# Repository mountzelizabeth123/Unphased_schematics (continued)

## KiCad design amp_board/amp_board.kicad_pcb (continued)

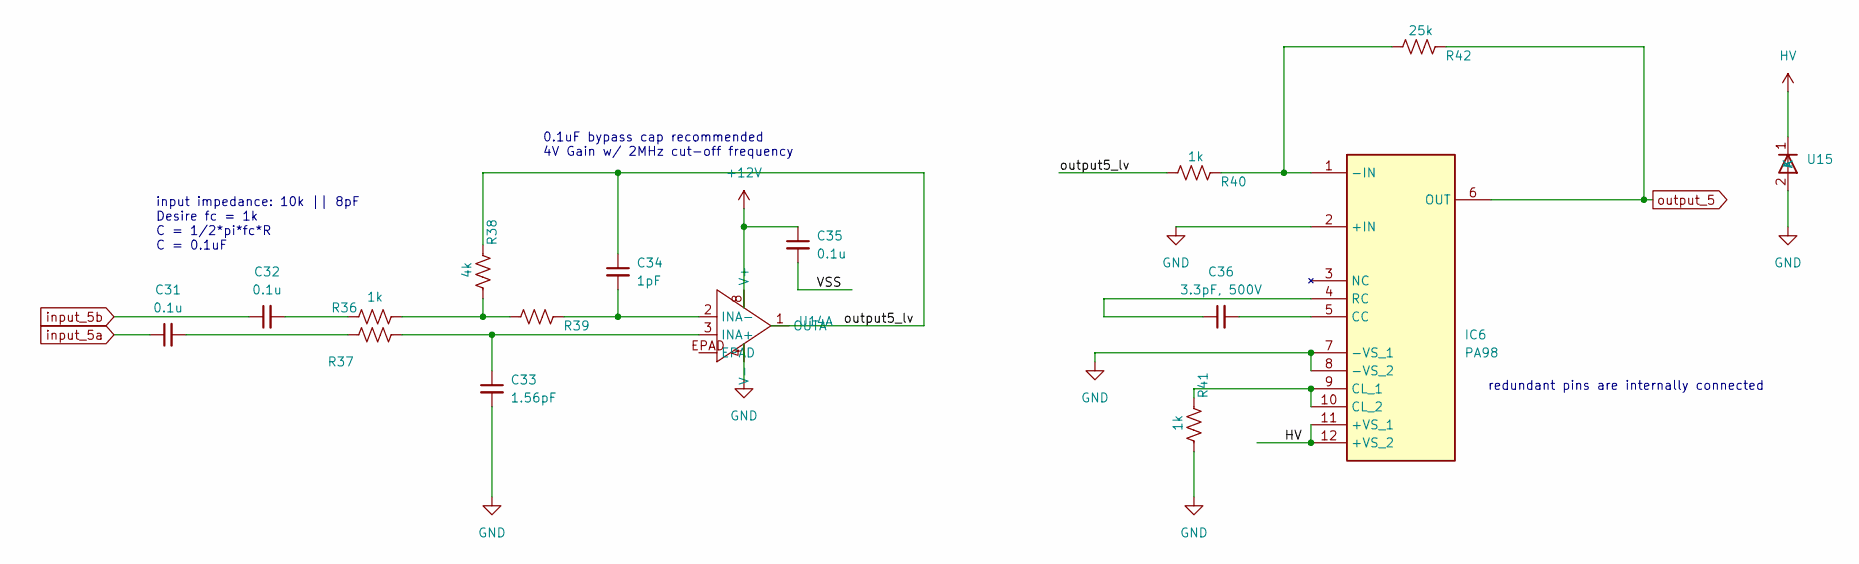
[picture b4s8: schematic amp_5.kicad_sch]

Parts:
C31, C32, C35: 0.1u; C_0603_1608Metric
C33: 1.56pF; C_0603_1608Metric
C34: 1pF; C_0603_1608Metric
C36: 3.3pF, 500V; C_0805_2012Metric
IC6: PA98; Mouser Part Number 137-PA98
R36, R40, R41: 1k; R_0603_1608Metric
R37, R39: R_US; R_0603_1608Metric
R38: 4k; R_0603_1608Metric
R42: 25k; R_0603_1608Metric
U14: OPA2211AIDDAR_L
U15: SMCJ150A-13-F

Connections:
+12V: C35.1, U14.8 (V+); also elsewhere on the board
/amp_5/VSS: C35.2
/amp_5/output5_lv: C34.1, R38.1, R40.2, U14.1 (OUTA)
GND: C33.2, IC6.2 (+IN), IC6.7 (-VS_1), IC6.8 (-VS_2), R41.2, U14.4 (V-), U15.2 (A); also elsewhere on the board
HV: IC6.11 (+VS_1), IC6.12 (+VS_2), U15.1 (K); also elsewhere on the board
unnamed: C31.2, R37.2
unnamed: C32.2, R36.2
unnamed: IC6.1 (-IN), R40.1, R42.2
unnamed: C36.2, IC6.5 (CC)
unnamed: IC6.9 (CL_1), IC6.10 (CL_2), R41.1
unnamed: C36.1, IC6.4 (RC)
unnamed: R36.1, R38.2, R39.2
unnamed: C33.1, R37.1, U14.3 (INA+)
unnamed: C34.2, R39.1, U14.2 (INA-)
input_5a: C31.1; also elsewhere on the board
input_5b: C32.1; also elsewhere on the board
output_5: IC6.6 (OUT), R42.1; also elsewhere on the board

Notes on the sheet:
redundant pins are internally connected
input impedance: 10k || 8pF Desire fc = 1k C = 1/2*pi*fc*R C = 0.1uF
0.1uF bypass cap recommended
4V Gain w/ 2MHz cut-off frequency

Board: 4 copper layers, 122 parts (0 on the bottom side), 81 nets, no tracks yet.

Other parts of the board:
J4, J6: SMA_RF2-04A-T-00-50-G; CONN_RF2-04A-T-00-50-G_ADM

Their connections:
GND: J4.2, J4.3 (Ext), J4.4 (Ext), J4.5 (Ext), J6.2, J6.3 (Ext), J6.4 (Ext), J6.5 (Ext); also elsewhere on the board
input_0a: J4.1; also elsewhere on the board
input_0b: J6.1; also elsewhere on the board

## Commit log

2024-09-24 Icurrent and ADC schem
2024-09-24 ADC swap for multi-channel opamp
2024-09-28 add .gitignore for kicad projects
2024-09-28 reorg repo
2024-09-28 added huxley; removed .DS_Store mac filesystem files from repo; add .DS_Store to .gitignore
2024-09-28 added blank README
2024-09-28 made the README a md file like it should have been
2024-09-28 added analog chip schematics and connector footprints
2024-09-29 updated Ibias gen and footprints
2024-09-29 updated footprints
2024-10-01 layout
2024-10-01 layout_1
2024-10-01 layout_2
2024-10-01 added banana plugs and fixed analog discovery pinout
2024-10-03 layout_1003
2024-10-03 layout_1003_1
2024-10-03 layout_1003_2
2024-10-05 reorganized pin assignment to level shifter; matched 3V3 power net name; minor schematic cleanup
2024-10-05 quick remap of 30pin
2024-10-08 fixed all bad refs; replaced analog discovery connector; change level shifter 3v3 to from analog discovery
2024-10-08 move most labels to correct f.silkscreen layer
2024-10-10 layout_1010
2024-10-10 minor schematic cleanup; addition of mounting holes; minor layout adjustment
2024-10-13 changed output names to be kicad diffpair-style (+/-); board rearrangement wip
2024-10-18 temp mid-rearrange
2024-10-20 general rerrange struct inpl
2024-10-20 pre edgechange
2024-10-20 I can't believe it's not butter
2024-10-22 prettier; manufacturing outputs
2024-10-22 added DNP prop to some caps and updated bom; added regular and rounded board outputs
2024-10-22 added .csv files (boms, footprint pos .csvs)
2024-10-23 amp board
2024-10-23 huxley bom updated
2024-10-23 add sierra format bom for huxley v1
2024-11-08 removed all via-in-pad; added CLK connection to analogdiscovery signal generator
2024-11-08 updated huxley-rounded to v1.1
2024-11-08 updated outputs for huxley v1.1
2024-11-08 amp board routed-need to fix mask aperture on ribbon cable connect
2024-11-08 minor update
2024-11-12 rev 3 routing
2024-11-12 routing complete
2024-11-12 all routed
2024-11-14 updated ground references in schematic
2024-11-14 ground reference pcb placement
2024-11-14 added polygons for ground reference
2024-11-15 updates based on 11/14 meeting
2024-11-15 detailed adjustments
2024-11-15 fixed disconnected nets
2024-11-16 final fabrication generated
2024-11-16 extra folder
2024-11-19 DFA fixes; bump huxley version number to v1.1.1; added updated BOM v1.1.1
